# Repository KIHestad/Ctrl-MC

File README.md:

# Motorcycle Control System

Ctrl MC (pronounced: "Control MC") is a system currently in development for simplifying and modernizing the wiring for motorcycles.

The project is managed by [KI Hestad](https://youtube.com/kihestad).
For updated information about the project check the authors [YouTube channel](https://youtube.com/kihestad). Feel free to participate with ideas and feedback by joining the projects [Discord Server](https://discord.gg/p5pfdZxfS8)

PCBs for this project are sponsored by [NextPCB](https://www.nextpcb.com?code=kihestad). If you need PCB manufacturing services, we recommend [NextPCB](https://www.nextpcb.com?code=kihestad).

Do you want to support this project? It's easy, just [click here to subscribe to the YouTube channel](https://youtube.com/kihestad/?sub_confirmation=1)!!!

## Project Description

This project is still in early stages, the idea is to:

* Create a motorcycle control system based on microcontrollers (STM32) and canbus to simplify and improve the wiring harness with possibility to add modern features for 'classic' (=older) motorcycles
  * The main goal is to make an intuitive and reliable system for wiring up a motorcycles lights and instruments 
  * The project does not in the first phases aim to replace or modify the motorcycle engine ignition system, but maybe later?
* Provide software, schematics and instructions free of charge
* Create a community for motorcycle- and Arduino enthusiasts that want to contribute
* Make the solution universal and configurable, it should be suitable for as many motorcycle brands and models as possible

Long term goals, depending on the success of the project:
* Provide a DIY kit with all parts needed
* Provide a completely built solution ready to be installed on the bike

Some of the benefits the system (hopefully) will give:

* Reliability: Individual solid state relays with inbuilt automatic fuses controls 12V to the bikes electrical components
* Simplify wiring: Single cable per component, separat wiring for input controls on handlebar and output power to components
* Providing customization: Setting parameters to enable features and how they should work
* Gives posibility to improve or add new features to the motorcycle (optional): 
  * Touch buttons instead of traditional handlebar switches
  * Keyless ignition using bluetooth, RF-ID or "password" using input buttons
  * OLED display instead of traditional speedometer, tachometer and warning lights
  * Smart functions, ex: auto turn off indicator lights, not possible to trigger start motor when engine is running
  * Alarm if bike is moved
* Use standard components
* Provide a budget friendly solution as an alternative to expensive commercial products

## Development information

The software is developed using Visual Studio Code. The first prototypes where using are using Platform IO, Arduino framework and C++ language. The latest prototype is using STM32CubeIDE and C language. The software is open source and available in this GitHub repository.
* Prototype 1 was a first attempt having a display unit and a relay unit using serial communication to send data in between
* Prototype 2 was a standalone display unit for testing use of hall sensor for speedometer and IT sensor for rpm meter made for a Cagiva 750 Elefant.
* Prototype 3 is a simple canbus communication test using STM32 microcontroller, this is not to be used in further development but just for testing the canbus communication
* MC Wiring Simulator is a PCB designed as a supportng tool for testing and developing purposes. 

## Other info

Let me know if anything is missing, just go to the project [Discord channel](https://discord.gg/p5pfdZxfS8) ^_^

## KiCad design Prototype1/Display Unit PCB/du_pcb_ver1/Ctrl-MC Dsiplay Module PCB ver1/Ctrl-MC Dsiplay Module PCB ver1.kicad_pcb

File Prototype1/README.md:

# Arduino Motorcycle Controller Software - PROTOTYPE 1

This is the first prototype from October 2021. It was based on two units: Relay Unit + Display Unit, with serial communication in between. It was never made any custom PCB for this version, it was mostly about learning and testing development boards. The software used the Arduino Framework and was made for the 30 pin EPRESSIF development boards with the microcontroller: ESP32-WROOM-32.

Check here for more info: https://youtu.be/3W9Y04q-X2k?si=rUN0Ap0xaVJPVOeV

This approch was abondoned in 2025 in favor of making it more flexible and by using canbus several units can be attached.

The new plan was explained here: https://youtu.be/J_AsExU7qkA?si=yqhxXnDfag6Xr95b

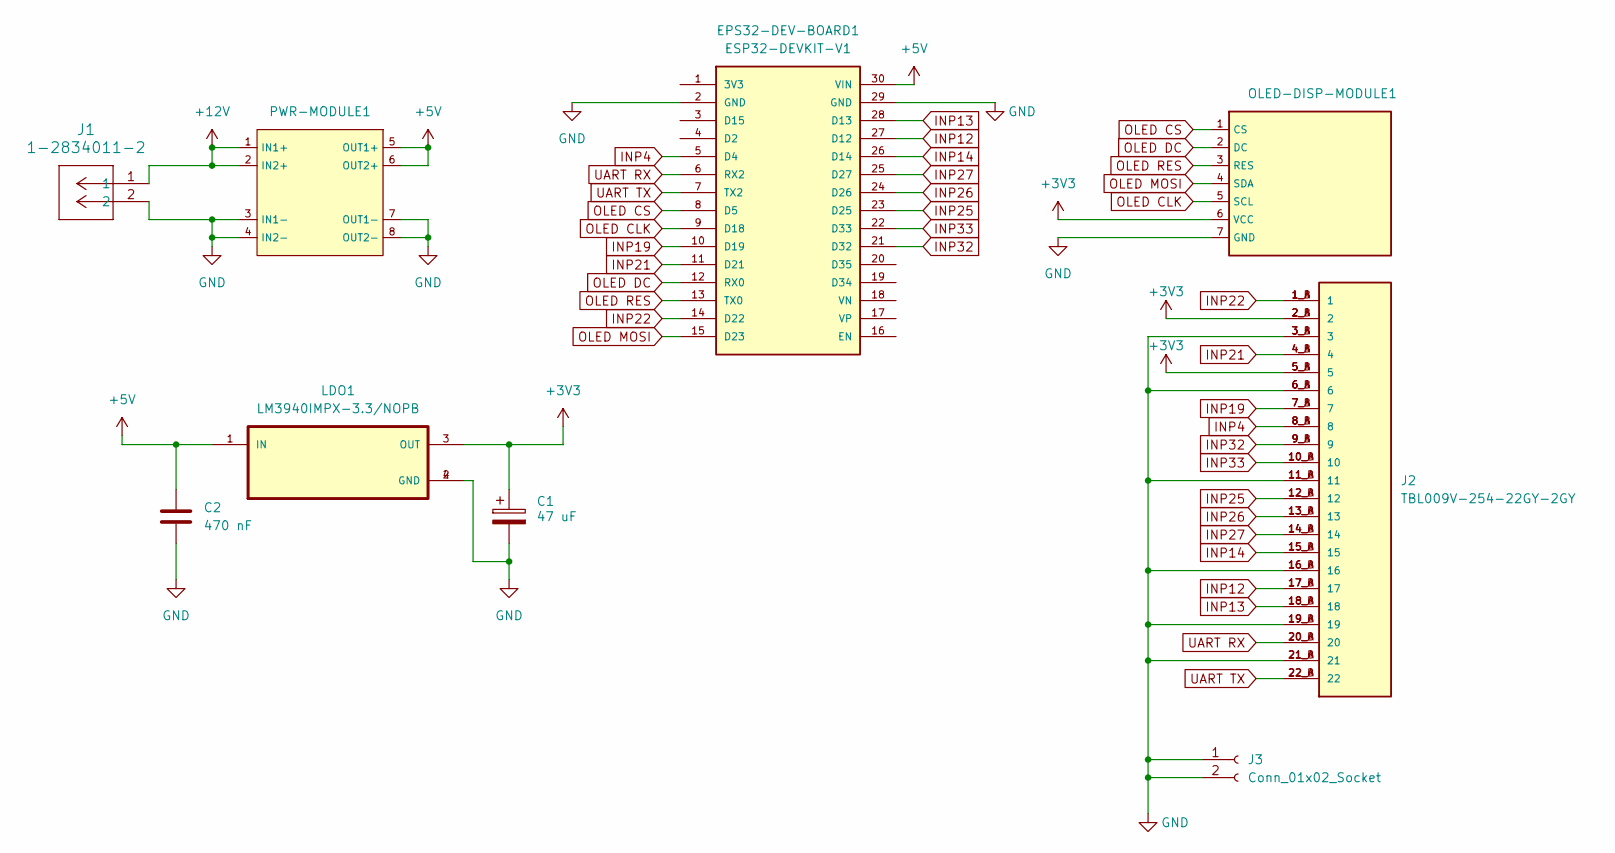
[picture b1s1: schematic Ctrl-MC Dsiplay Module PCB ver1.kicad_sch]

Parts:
C1: 47 uF; CP_EIA-6032-15_Kemet-U_Pad2.25x2.35mm_HandSolder
C2: 470 nF; C_1210_3225Metric_Pad1.33x2.70mm_HandSolder
EPS32-DEV-BOARD1: ESP32-DEVKIT-V1; MODULE_ESP32_DEVKIT_V1
J1: 1-2834011-2; CONN2_1-2834011-2_TEC
J2: TBL009V-254-22GY-2GY; CUI_TBL009V-254-22GY-2GY
J3: Conn_01x02_Socket; JST_EH_B2B-EH-A_1x02_P2.50mm_Vertical
LDO1: LM3940IMPX-3.3/NOPB; SOT230P700X180-4N
OLED-DISP-MODULE1: OLED Display 2.42
PWR-MODULE1: Mini DC-DC PWR MODULE 3A

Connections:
+3V3: C1.1, J2.2_A (2), J2.2_B (2), J2.5_A (5), J2.5_B (5), LDO1.3 (OUT), OLED-DISP-MODULE1.6 (VCC)
+5V: C2.1, EPS32-DEV-BOARD1.30 (VIN), LDO1.1 (IN), PWR-MODULE1.5 (OUT1+), PWR-MODULE1.6 (OUT2+)
+12V: J1.1, PWR-MODULE1.1 (IN1+), PWR-MODULE1.2 (IN2+)
GND: C1.2, C2.2, EPS32-DEV-BOARD1.2 (GND), EPS32-DEV-BOARD1.29 (GND), J1.2, J2.3_A (3), J2.3_B (3), J2.6_A (6), J2.6_B (6), J2.11_A (11), J2.11_B (11), J2.16_A (16), J2.16_B (16), J2.19_A (19), J2.19_B (19), J2.21_A (21), J2.21_B (21), J3.1, J3.2, LDO1.2 (GND), LDO1.4 (GND), OLED-DISP-MODULE1.7 (GND), PWR-MODULE1.3 (IN1-), PWR-MODULE1.4 (IN2-), PWR-MODULE1.7 (OUT1-), PWR-MODULE1.8 (OUT2-)
INP4: EPS32-DEV-BOARD1.5 (D4), J2.8_A (8), J2.8_B (8)
INP12: EPS32-DEV-BOARD1.27 (D12), J2.17_A (17), J2.17_B (17)
INP13: EPS32-DEV-BOARD1.28 (D13), J2.18_A (18), J2.18_B (18)
INP14: EPS32-DEV-BOARD1.26 (D14), J2.15_A (15), J2.15_B (15)
INP19: EPS32-DEV-BOARD1.10 (D19), J2.7_A (7), J2.7_B (7)
INP21: EPS32-DEV-BOARD1.11 (D21), J2.4_A (4), J2.4_B (4)
INP22: EPS32-DEV-BOARD1.14 (D22), J2.1_A (1), J2.1_B (1)
INP25: EPS32-DEV-BOARD1.23 (D25), J2.12_A (12), J2.12_B (12)
INP26: EPS32-DEV-BOARD1.24 (D26), J2.13_A (13), J2.13_B (13)
INP27: EPS32-DEV-BOARD1.25 (D27), J2.14_A (14), J2.14_B (14)
INP32: EPS32-DEV-BOARD1.21 (D32), J2.9_A (9), J2.9_B (9)
INP33: EPS32-DEV-BOARD1.22 (D33), J2.10_A (10), J2.10_B (10)
OLED CLK: EPS32-DEV-BOARD1.9 (D18), OLED-DISP-MODULE1.5 (SCL)
OLED CS: EPS32-DEV-BOARD1.8 (D5), OLED-DISP-MODULE1.1 (CS)
OLED DC: EPS32-DEV-BOARD1.12 (RX0), OLED-DISP-MODULE1.2 (DC)
OLED MOSI: EPS32-DEV-BOARD1.15 (D23), OLED-DISP-MODULE1.4 (SDA)
OLED RES: EPS32-DEV-BOARD1.13 (TX0), OLED-DISP-MODULE1.3 (RES)
UART RX: EPS32-DEV-BOARD1.6 (RX2), J2.20_A (20), J2.20_B (20)
UART TX: EPS32-DEV-BOARD1.7 (TX2), J2.22_A (22), J2.22_B (22)

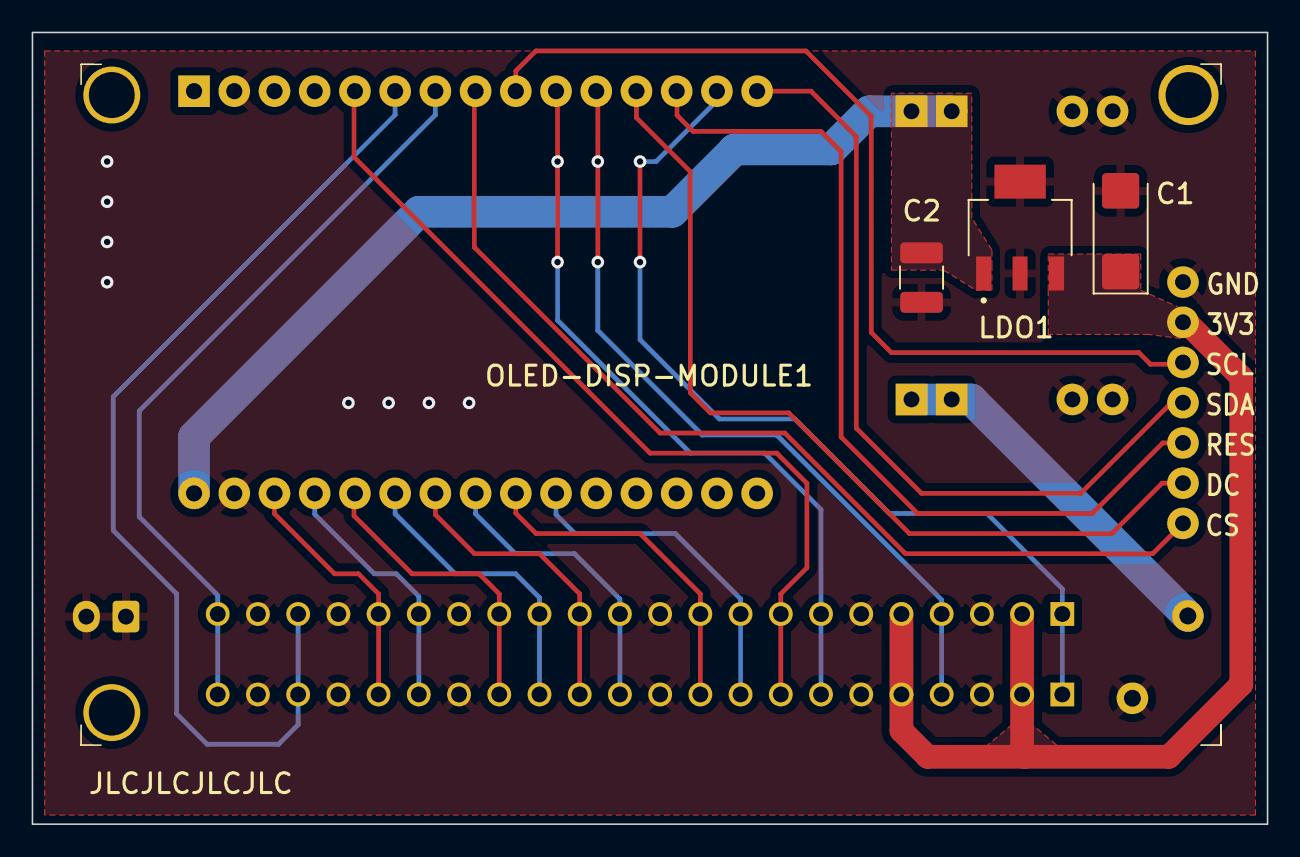
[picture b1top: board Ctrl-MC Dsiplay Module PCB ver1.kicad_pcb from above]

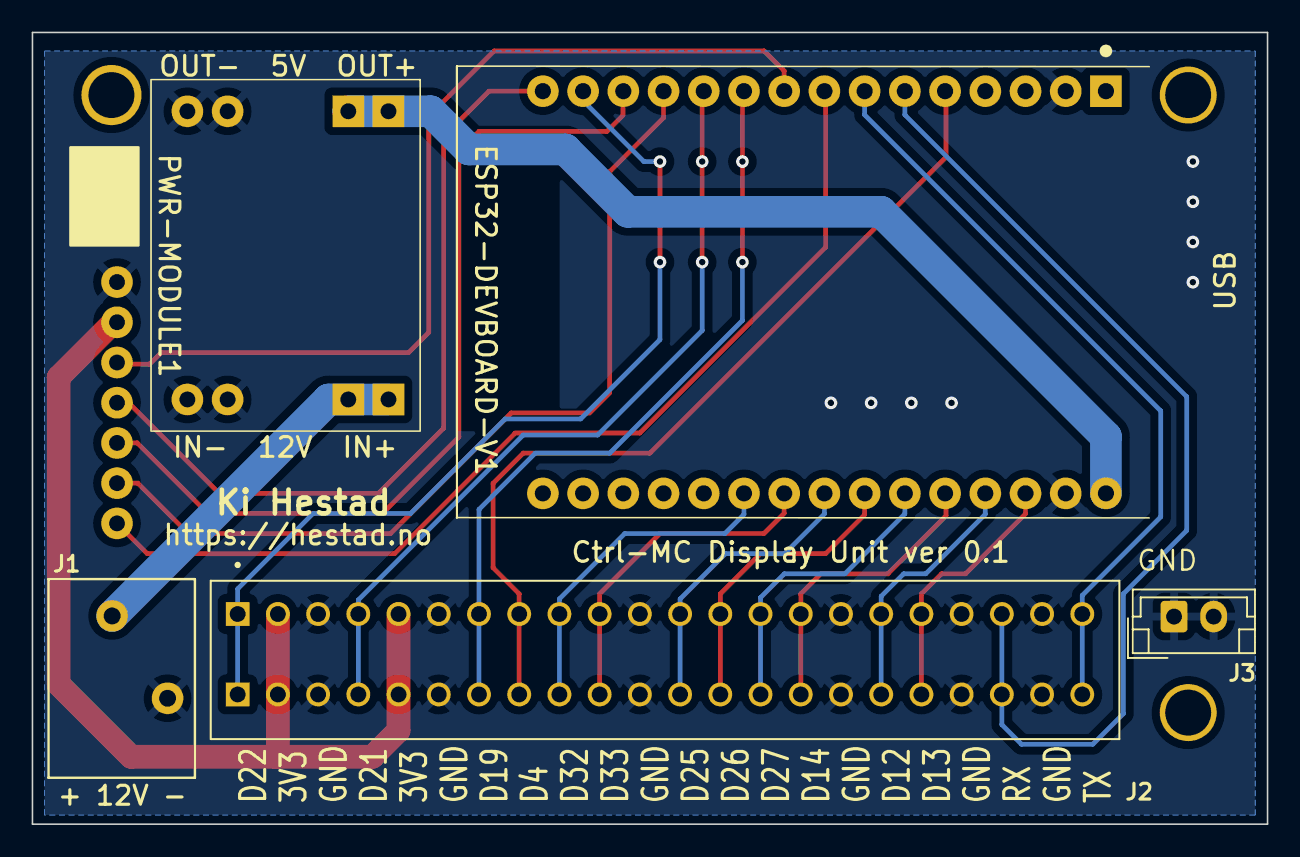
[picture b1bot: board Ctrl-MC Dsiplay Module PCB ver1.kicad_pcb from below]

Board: 2 copper layers, 78.0 x 50.0 mm, 9 parts (5 on the bottom side), 23 nets.

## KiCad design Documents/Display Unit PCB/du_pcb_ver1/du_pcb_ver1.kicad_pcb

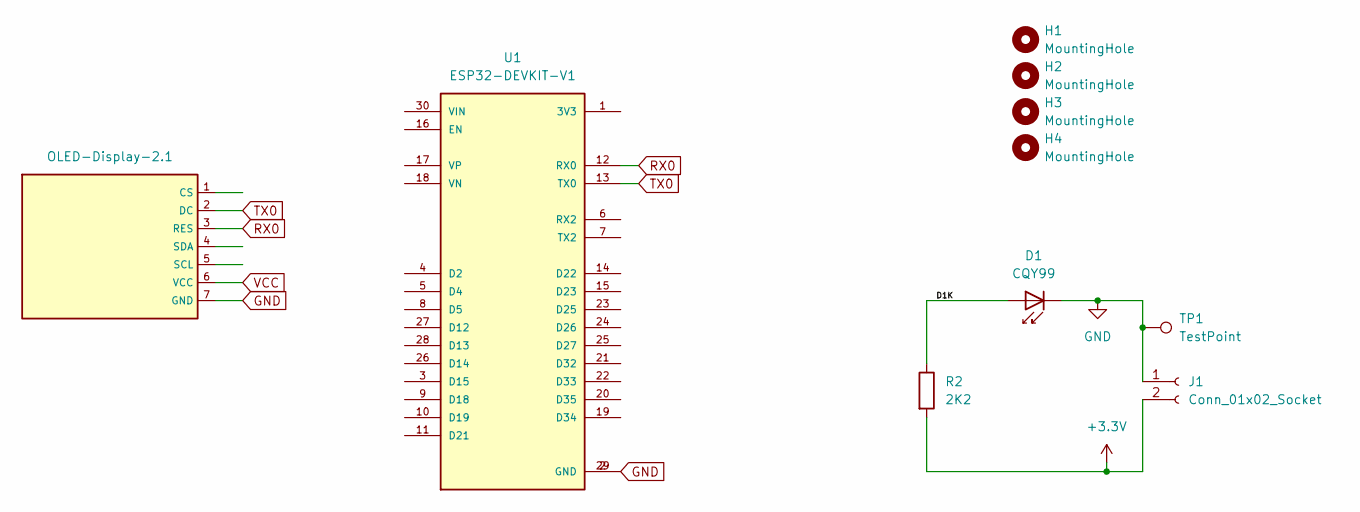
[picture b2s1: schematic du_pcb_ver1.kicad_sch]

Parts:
D1: CQY99; LED_D5.0mm_IRGrey
H1, H2, H3, H4: MountingHole; MountingHole_3.2mm_M3
J1: Conn_01x02_Socket; PinHeader_1x02_P2.54mm_Vertical
OLED-Display-2.1: OLED Display 2.42
R2: 2K2; R_Axial_DIN0207_L6.3mm_D2.5mm_P10.16mm_Horizontal
TP1: TestPoint; TestPoint_THTPad_2.0x2.0mm_Drill1.0mm
U1: ESP32-DEVKIT-V1; MODULE_ESP32_DEVKIT_V1; PARTREV N/A

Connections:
+3.3V: J1.2, R2.2
/D1K: D1.2 (A), R2.1
GND: D1.1 (K), J1.1, OLED-Display-2.1.7 (GND), TP1.1, U1.2 (GND), U1.29 (GND)
RX0: OLED-Display-2.1.3 (RES), U1.12 (RX0)
TX0: OLED-Display-2.1.2 (DC), U1.13 (TX0)
VCC: OLED-Display-2.1.6 (VCC)

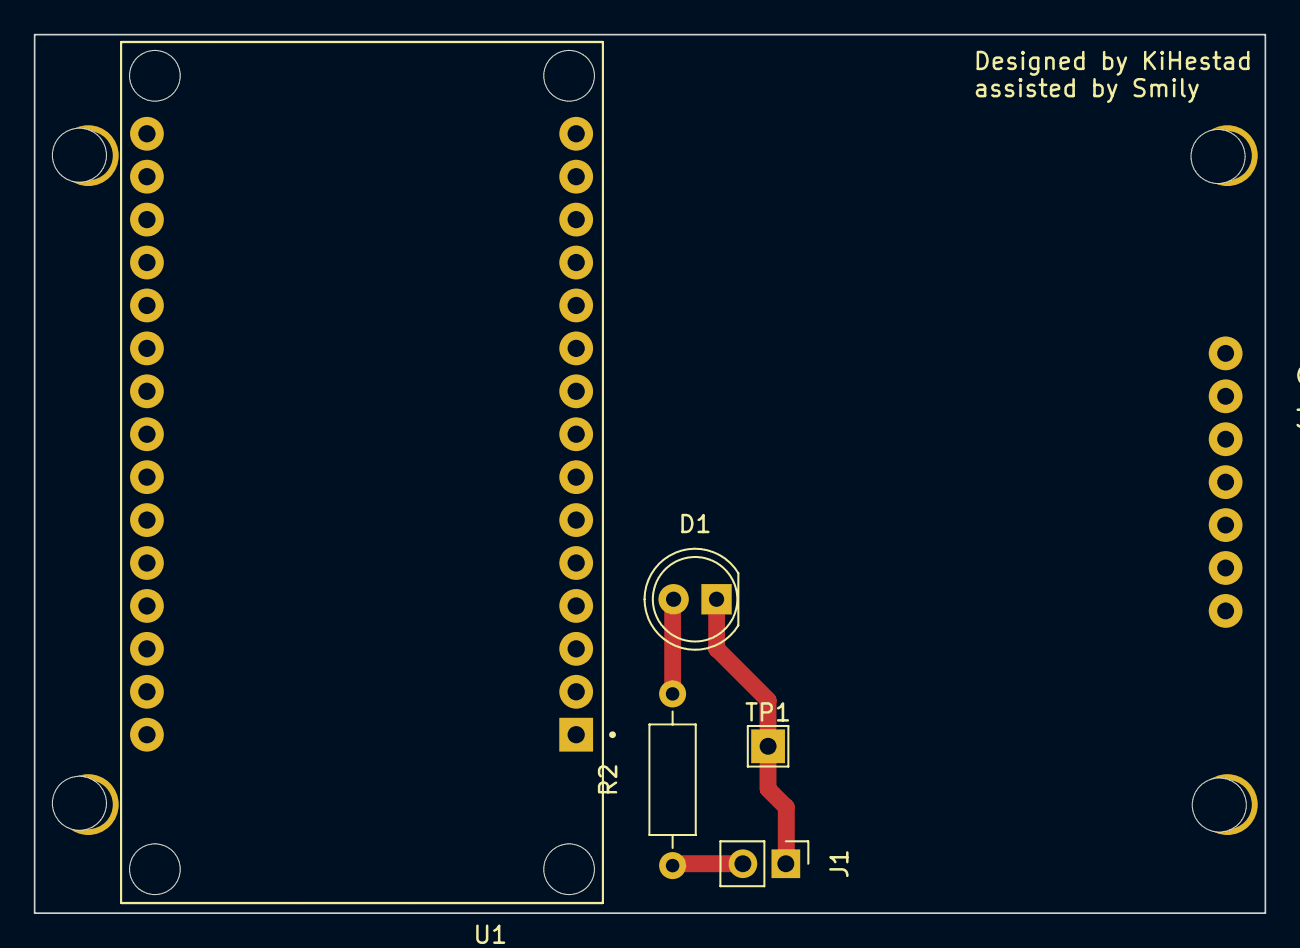
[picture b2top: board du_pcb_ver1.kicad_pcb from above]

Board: 2 copper layers, 72.8 x 52.0 mm, 10 parts (1 on the bottom side), 5 nets.

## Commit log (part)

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2021-09-13 Changed GitHub default c++ ignore file to Visual Studio Code default ignore file
2021-09-13 Initial commit, project still in early dev phase
2021-09-13 Updated readme.md with some initial thoughts about the project
2021-09-13 Added some project info
2021-09-13 Improved documentation
2021-09-14 Changed project name, the old one was a bit boring ^_^
2021-09-14 Not just changing project name, but also reworking most of the user configuration structure
2021-09-14 Updated readme text
2021-09-14 Cleanup code after restructuring the _config.h file for more conveniant ux
2021-09-14 typos in the readme file :-/
2021-09-14 small layot change
2021-09-15 Implemented ignition on using password (from buttons)
2021-09-15 Reworked button method, restructuring a lot, not tested yet
2021-09-17 Moved all files to subfolder, first attemt is now moved to: Prototype_ver1
2021-09-19 Implemented basic startup features for the handlebar unit
2021-09-19 VS Code wants to put git ignore file in each project folder, added a copy to root
2021-09-20 Major improvement: implemented serial communication between Handlebar unit and Relay unit
2021-09-20 Missing file from prev commit
2021-09-22 Improved serial communication, hb-unit and r-unit now communication successfully, implemented handshake function
2021-09-22 Added header on all code files
2021-09-24 Improved for using NodeMCU as handlebar unit, implemented display menu control
2021-09-25 Improved some icons, stared adding handlebar button controls (HiLo)
2021-09-26 Reworked ignition on/off and lights images, cleaner layout, also some minor improvementt here and there
2021-10-02 Implemented several new features, refactored code
2021-10-02 Added some first example images to the documents folder
2021-10-02 Small fix, disable goto status page when status page is selected
2021-10-03 Minor bugfixes and improvements
2021-10-05 Implemented shared code as local library in new project: "Common", implemented for relay unit, TBD for handlebar unit Refacored relay unit project, each classes separated / not dependent on other cla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
2021-10-05 Removed first prototype project, added getting-started document (draft)
2021-10-05 temp file rename fix
2021-10-05 rename file
2021-10-06 Implemented use of common library for handlebar unit, tested the new common serial communication library
2021-10-06 Moved config file to inclide folder
2021-10-23 Reworked Handlebar Unit to work with ESP32, Started moving config as common library, improved code for relay unit.
2021-11-12 Massive rework, still in progress.
2021-11-12 Updated the dev log
2021-11-12 Updated HW recommendations
2021-11-16 New reworked code after restructuring, initial testing done, working version
2021-11-16 Small improvements/bugfixes regarding last commit
2021-12-02 Several bugfixes after system test, added temperature sensor
2021-12-03 Updated info
2021-12-03 Added new display menu item for starter motor
2022-02-12 Reworked using u8g2 OLED library
2022-04-12 Added original wiring diagram for Honda CB400N CB250N Super Dream
2023-07-03 Added images to beta ver 2
2023-07-22 Updated documents, PCB for display unit beta ver 0.1
2023-07-22 gitignore and new workspace file
2023-07-22 Woriking on new version, this is a non functional commit
2023-09-20 Update2 README.md
2023-09-20 Update3 README.md
2023-09-20 Marketing Images
2025-09-28 New/&changed marketing images
2025-09-28 Refactoring, moving old code to: Prototype1
2025-09-28 Upgraded old project
2025-09-28 Upgraded old libs
2025-09-28 New Prototype 2: Head Unit (speedo & tach)
2025-09-28 improved git ignore
2025-09-28 Cleanup .vscode files, included by mistake
2025-09-28 Removed test folder, a tiny but tidying
2025-09-28 Implemented RPM as progressbar
2025-09-28 Added support for hum/temp sensor + elefant logo
2025-09-28 Bugfixes for trip counters and fuel consumption calc
2025-09-28 Bigger font for RPM, small layout improvements
2025-10-12 Implemented RPM meter
2025-10-13 Cleanup unused properties
2025-11-29 Ported to STM32
2025-12-16 Small improvements
2025-12-16 Refactoring after prototype 2
2025-12-16 typo fix README.md
2025-12-23 Added Prototype 3
2026-01-11 Refactored, moved code to SRC folder
2026-01-11 Refactored Prototype 2, moded code to SRC folder
2026-01-11 Updated Git Ignore
2026-01-11 Added KiCad Project for prototype
2026-01-11 Moved code to SRC folder
2026-01-11 Added KiCad Project
2026-01-21 Fixes some minor typos in Readme.md
2026-01-24 Added MC Wiring Sim Project
2026-01-24 Incl img of the MC Wiring Sim PCB
2026-01-25 Fixed typos
2026-01-25 Fix typos2
2026-02-14 Updated images and readme
2026-02-25 Added prototype 4, still in progress
2026-02-25 Improved prototype info
2026-02-25 Fix path for compiling after changing folder
2026-02-26 First test version fully working
2026-03-02 Updated readme after YT video published
2026-03-02 Added blinker feature
2026-03-11 Renamed files to separate custom code from hal
2026-03-16 Experimenting designing a global config
2026-04-06 Added CANBUS message support structure using DBC-file
2026-04-06 Temp Commit, refactoring - not a running code
2026-04-22 Massive cleanup, removed a lot of AI generated code
2026-04-24 Added canbus manager for send/receive messages + file descr
2026-04-25 Improved stm32 config (160Mhz ) canbus config and methods
2026-04-25 Made method for saving trip- and total-km to flash
2026-04-25 improved canbus message db file
2026-05-10 Another refactoring, searate folder and files for input logic
2026-05-10 rearranged cmake build file list
2026-05-10 updated can db
2026-05-10 can message improvements
2026-05-14 Cleanup and improved info
2026-05-14 restructured startup methods
2026-05-14 cleanup statup procedure - bugfixes
2026-05-14 moved cmc_config_unit_info to separate variable
2026-05-16 Improved AI agent setup
2026-05-16 Temp restructure for app-state
2026-05-16 refactor app state
2026-05-16 improved illustration
2026-05-16 Improved descr
2026-05-16 added on build size of config
2026-05-16 Improved config types
2026-05-16 cleanup and renamed methods
2026-05-16 first version complete feature logic with can
2026-05-16 improved ai instructions
2026-05-16 added features for first test
2026-05-16 bugfix
2026-05-20 Added feature for direction indicator
2026-05-20 fix: V-004 security vulnerability
    Automated security fix generated by OrbisAI Security
2026-05-21 Improved docs
2026-05-21 removed old doc img
2026-05-21 Rework logic
2026-05-21 bugfix turn signal feature
2026-05-21 ded features
2026-05-21 added features
2026-05-21 added fueatures
2026-05-23 Initial commit - CanSniffer
2026-05-23 Setup missing cmpiler flags
2026-05-23 updated docs
2026-05-23 Vibe coded CanSniffer based on user promts and instructions
2026-05-23 fix faulty config
2026-05-23 fixes after review
2026-05-23 avoid turn signals to drift out of sync
2026-05-24 Added LED functions
2026-05-24 Bugfixes
2026-05-24 Updated readme for the final version of the CanSniffer
